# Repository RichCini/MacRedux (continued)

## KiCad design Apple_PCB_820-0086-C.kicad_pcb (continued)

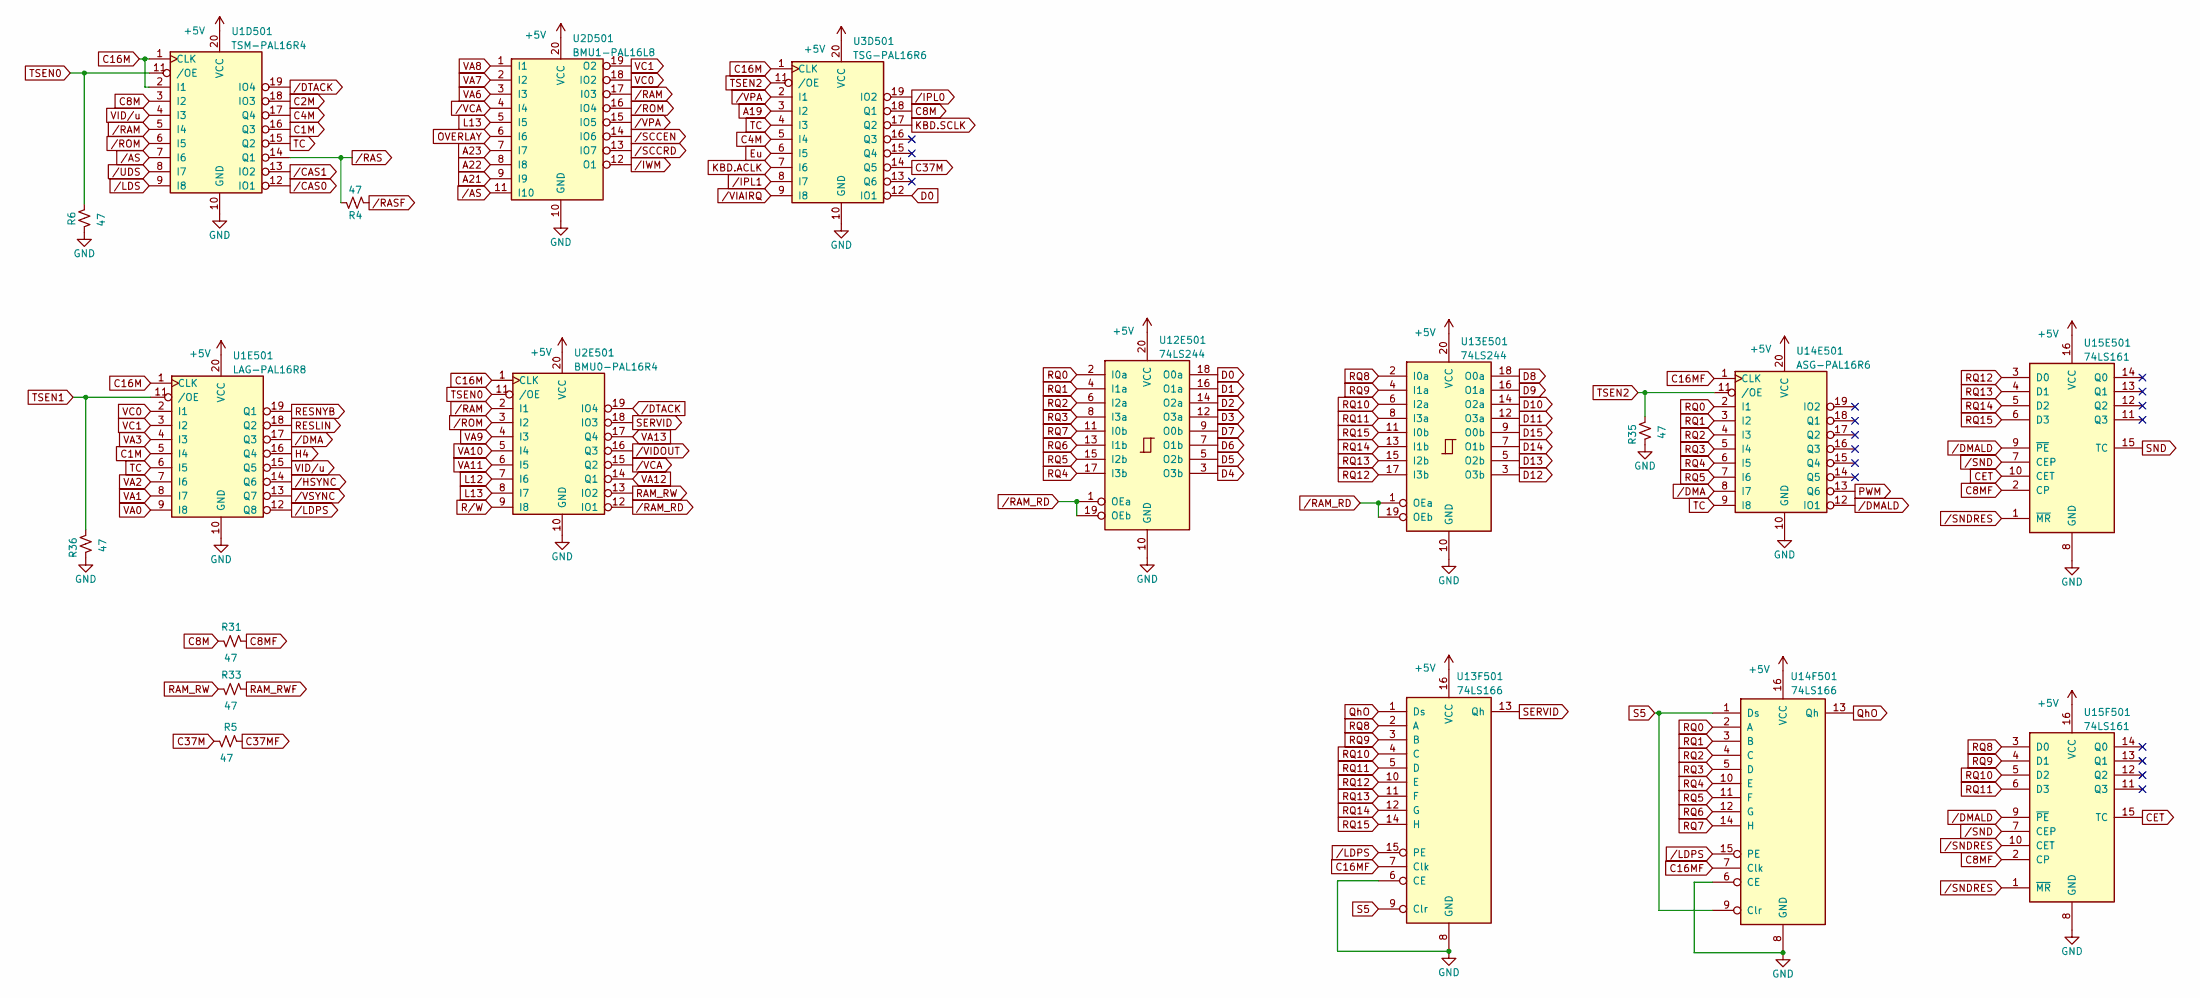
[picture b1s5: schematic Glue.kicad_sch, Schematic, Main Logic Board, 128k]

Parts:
R4, R5, R6, R31, R33, R35, R36: 47; R_Axial_DIN0207_L6.3mm_D2.5mm_P7.62mm_Horizontal
U1D501: TSM-PAL16R4; DIP-20_W7.62mm_Socket_LongPads
U1E501: LAG-PAL16R8; DIP-20_W7.62mm_Socket_LongPads
U2D501: BMU1-PAL16L8; DIP-20_W7.62mm_Socket_LongPads
U2E501: BMU0-PAL16R4; DIP-20_W7.62mm_Socket_LongPads
U3D501: TSG-PAL16R6; DIP-20_W7.62mm_Socket_LongPads
U12E501, U13E501: 74LS244; DIP-20_W7.62mm_Socket_LongPads
U13F501, U14F501: 74LS166; DIP-16_W7.62mm_Socket_LongPads
U14E501: ASG-PAL16R6; DIP-20_W7.62mm_Socket_LongPads
U15E501, U15F501: 74LS161; DIP-16_W7.62mm_Socket_LongPads

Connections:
+5V: U1D501.20 (VCC), U1E501.20 (VCC), U2D501.20 (VCC), U2E501.20 (VCC), U3D501.20 (VCC), U12E501.20 (VCC), U13E501.20 (VCC), U13F501.16 (VCC), U14E501.20 (VCC), U14F501.16 (VCC), U15E501.16 (VCC), U15F501.16 (VCC); also elsewhere on the board
A19: U3D501.3 (I2); also elsewhere on the board
A21: U2D501.9 (I9); also elsewhere on the board
A22: U2D501.8 (I8); also elsewhere on the board
A23: U2D501.7 (I7); also elsewhere on the board
C1M: U1D501.16 (Q3), U1E501.5 (I4)
C2M: U1D501.18 (IO3); also elsewhere on the board
C4M: U1D501.17 (Q4), U3D501.5 (I4)
C8M: R31.1, U1D501.3 (I2), U3D501.18 (Q1)
C8MF: R31.2, U15E501.2 (CP), U15F501.2 (CP); also elsewhere on the board
C16M: U1D501.1 (CLK), U1D501.2 (I1), U1E501.1 (CLK), U2E501.1 (CLK), U3D501.1 (CLK); also elsewhere on the board
C16MF: U13F501.7 (Clk), U14E501.1 (CLK), U14F501.7 (Clk); also elsewhere on the board
C37M: R5.1, U3D501.14 (Q5)
C37MF: R5.2; also elsewhere on the board
CET: U15E501.10 (CET), U15F501.15 (TC)
D0: U3D501.12 (IO1), U12E501.18 (O0a); also elsewhere on the board
D1: U12E501.16 (O1a); also elsewhere on the board
D2: U12E501.14 (O2a); also elsewhere on the board
D3: U12E501.12 (O3a); also elsewhere on the board
D4: U12E501.3 (O3b); also elsewhere on the board
D5: U12E501.5 (O2b); also elsewhere on the board
D6: U12E501.7 (O1b); also elsewhere on the board
D7: U12E501.9 (O0b); also elsewhere on the board
D8: U13E501.18 (O0a); also elsewhere on the board
D9: U13E501.16 (O1a); also elsewhere on the board
D10: U13E501.14 (O2a); also elsewhere on the board
D11: U13E501.12 (O3a); also elsewhere on the board
D12: U13E501.3 (O3b); also elsewhere on the board
D13: U13E501.5 (O2b); also elsewhere on the board
D14: U13E501.7 (O1b); also elsewhere on the board
D15: U13E501.9 (O0b); also elsewhere on the board
Eu: U3D501.6 (I5); also elsewhere on the board
GND: R6.1, R35.1, R36.1, U1D501.10 (GND), U1E501.10 (GND), U2D501.10 (GND), U2E501.10 (GND), U3D501.10 (GND), U12E501.10 (GND), U13E501.10 (GND), U13F501.6 (CE), U13F501.8 (GND), U14E501.10 (GND), U14F501.6 (CE), U14F501.8 (GND), U15E501.8 (GND), U15F501.8 (GND); also elsewhere on the board
H4: U1E501.16 (Q4); also elsewhere on the board
KBD.ACLK: U3D501.7 (I6); also elsewhere on the board
KBD.SCLK: U3D501.17 (Q2); also elsewhere on the board
L12: U2E501.7 (I6); also elsewhere on the board
L13: U2D501.5 (I5), U2E501.8 (I7); also elsewhere on the board
OVERLAY: U2D501.6 (I6); also elsewhere on the board
PWM: U14E501.13 (Q6); also elsewhere on the board
QhO: U13F501.1 (Ds), U14F501.13 (Qh)
RAM_RW: R33.1, U2E501.13 (IO2)
RAM_RWF: R33.2; also elsewhere on the board
RESLIN: U1E501.18 (Q2); also elsewhere on the board
RESNYB: U1E501.19 (Q1); also elsewhere on the board
RQ0: U12E501.2 (I0a), U14E501.2 (I1), U14F501.2 (A); also elsewhere on the board
RQ1: U12E501.4 (I1a), U14E501.3 (I2), U14F501.3 (B); also elsewhere on the board
RQ2: U12E501.6 (I2a), U14E501.4 (I3), U14F501.4 (C); also elsewhere on the board
RQ3: U12E501.8 (I3a), U14E501.5 (I4), U14F501.5 (D); also elsewhere on the board
RQ4: U12E501.17 (I3b), U14E501.6 (I5), U14F501.10 (E); also elsewhere on the board
RQ5: U12E501.15 (I2b), U14E501.7 (I6), U14F501.11 (F); also elsewhere on the board
RQ6: U12E501.13 (I1b), U14F501.12 (G); also elsewhere on the board
RQ7: U12E501.11 (I0b), U14F501.14 (H); also elsewhere on the board
RQ8: U13E501.2 (I0a), U13F501.2 (A), U15F501.3 (D0); also elsewhere on the board
RQ9: U13E501.4 (I1a), U13F501.3 (B), U15F501.4 (D1); also elsewhere on the board
RQ10: U13E501.6 (I2a), U13F501.4 (C), U15F501.5 (D2); also elsewhere on the board
RQ11: U13E501.8 (I3a), U13F501.5 (D), U15F501.6 (D3); also elsewhere on the board
RQ12: U13E501.17 (I3b), U13F501.10 (E), U15E501.3 (D0); also elsewhere on the board
RQ13: U13E501.15 (I2b), U13F501.11 (F), U15E501.4 (D1); also elsewhere on the board
RQ14: U13E501.13 (I1b), U13F501.12 (G), U15E501.5 (D2); also elsewhere on the board
RQ15: U13E501.11 (I0b), U13F501.14 (H), U15E501.6 (D3); also elsewhere on the board
R/W: U2E501.9 (I8); also elsewhere on the board
S5: U13F501.9 (Clr), U14F501.1 (Ds), U14F501.9 (Clr); also elsewhere on the board
SERVID: U2E501.18 (IO3), U13F501.13 (Qh)
SND: U15E501.15 (TC); also elsewhere on the board
TC: U1D501.15 (Q2), U1E501.6 (I5), U3D501.4 (I3), U14E501.9 (I8); also elsewhere on the board
TSEN0: R6.2, U1D501.11 (/OE), U2E501.11 (/OE)
TSEN1: R36.2, U1E501.11 (/OE)
TSEN2: R35.2, U3D501.11 (/OE), U14E501.11 (/OE)
VA0: U1E501.9 (I8); also elsewhere on the board
VA1: U1E501.8 (I7); also elsewhere on the board
VA2: U1E501.7 (I6); also elsewhere on the board
VA3: U1E501.4 (I3); also elsewhere on the board
VA6: U2D501.3 (I3); also elsewhere on the board
VA7: U2D501.2 (I2); also elsewhere on the board
VA8: U2D501.1 (I1); also elsewhere on the board
VA9: U2E501.4 (I3); also elsewhere on the board
VA10: U2E501.5 (I4); also elsewhere on the board
VA11: U2E501.6 (I5); also elsewhere on the board
VA12: U2E501.14 (Q1); also elsewhere on the board
VA13: U2E501.17 (Q4); also elsewhere on the board
VC0: U1E501.2 (I1), U2D501.18 (IO2)
VC1: U1E501.3 (I2), U2D501.19 (O2)
VID/u: U1D501.4 (I3), U1E501.15 (Q5); also elsewhere on the board
/AS: U1D501.7 (I6), U2D501.11 (I10); also elsewhere on the board
/CAS0: U1D501.12 (IO1); also elsewhere on the board
/CAS1: U1D501.13 (IO2); also elsewhere on the board
/DMA: U1E501.17 (Q3), U14E501.8 (I7); also elsewhere on the board
/DMALD: U14E501.12 (IO1), U15E501.9 (~PE), U15F501.9 (~PE)
/DTACK: U1D501.19 (IO4), U2E501.19 (IO4); also elsewhere on the board
/HSYNC: U1E501.14 (Q6); also elsewhere on the board
/IPL0: U3D501.19 (IO2); also elsewhere on the board
/IPL1: U3D501.8 (I7); also elsewhere on the board
/IWM: U2D501.12 (O1); also elsewhere on the board
/LDPS: U1E501.12 (Q8), U13F501.15 (PE), U14F501.15 (PE)
/LDS: U1D501.9 (I8); also elsewhere on the board
/RAM: U1D501.5 (I4), U2D501.17 (I03), U2E501.2 (I1)
/RAM_RD: U2E501.12 (IO1), U12E501.1 (OEa), U12E501.19 (OEb), U13E501.1 (OEa), U13E501.19 (OEb)
/RAS: R4.2, U1D501.14 (Q1)
/RASF: R4.1; also elsewhere on the board
/ROM: U1D501.6 (I5), U2D501.16 (IO4), U2E501.3 (I2); also elsewhere on the board
/SCCEN: U2D501.14 (IO6); also elsewhere on the board
/SCCRD: U2D501.13 (IO7); also elsewhere on the board
/SND: U15E501.7 (CEP), U15F501.7 (CEP); also elsewhere on the board
/SNDRES: U15E501.1 (~MR), U15F501.1 (~MR), U15F501.10 (CET); also elsewhere on the board
/UDS: U1D501.8 (I7); also elsewhere on the board
/VCA: U2D501.4 (I4), U2E501.15 (Q2)
/VIAIRQ: U3D501.9 (I8); also elsewhere on the board
/VIDOUT: U2E501.16 (Q3); also elsewhere on the board
/VPA: U2D501.15 (IO5), U3D501.2 (I1); also elsewhere on the board
/VSYNC: U1E501.13 (Q7); also elsewhere on the board

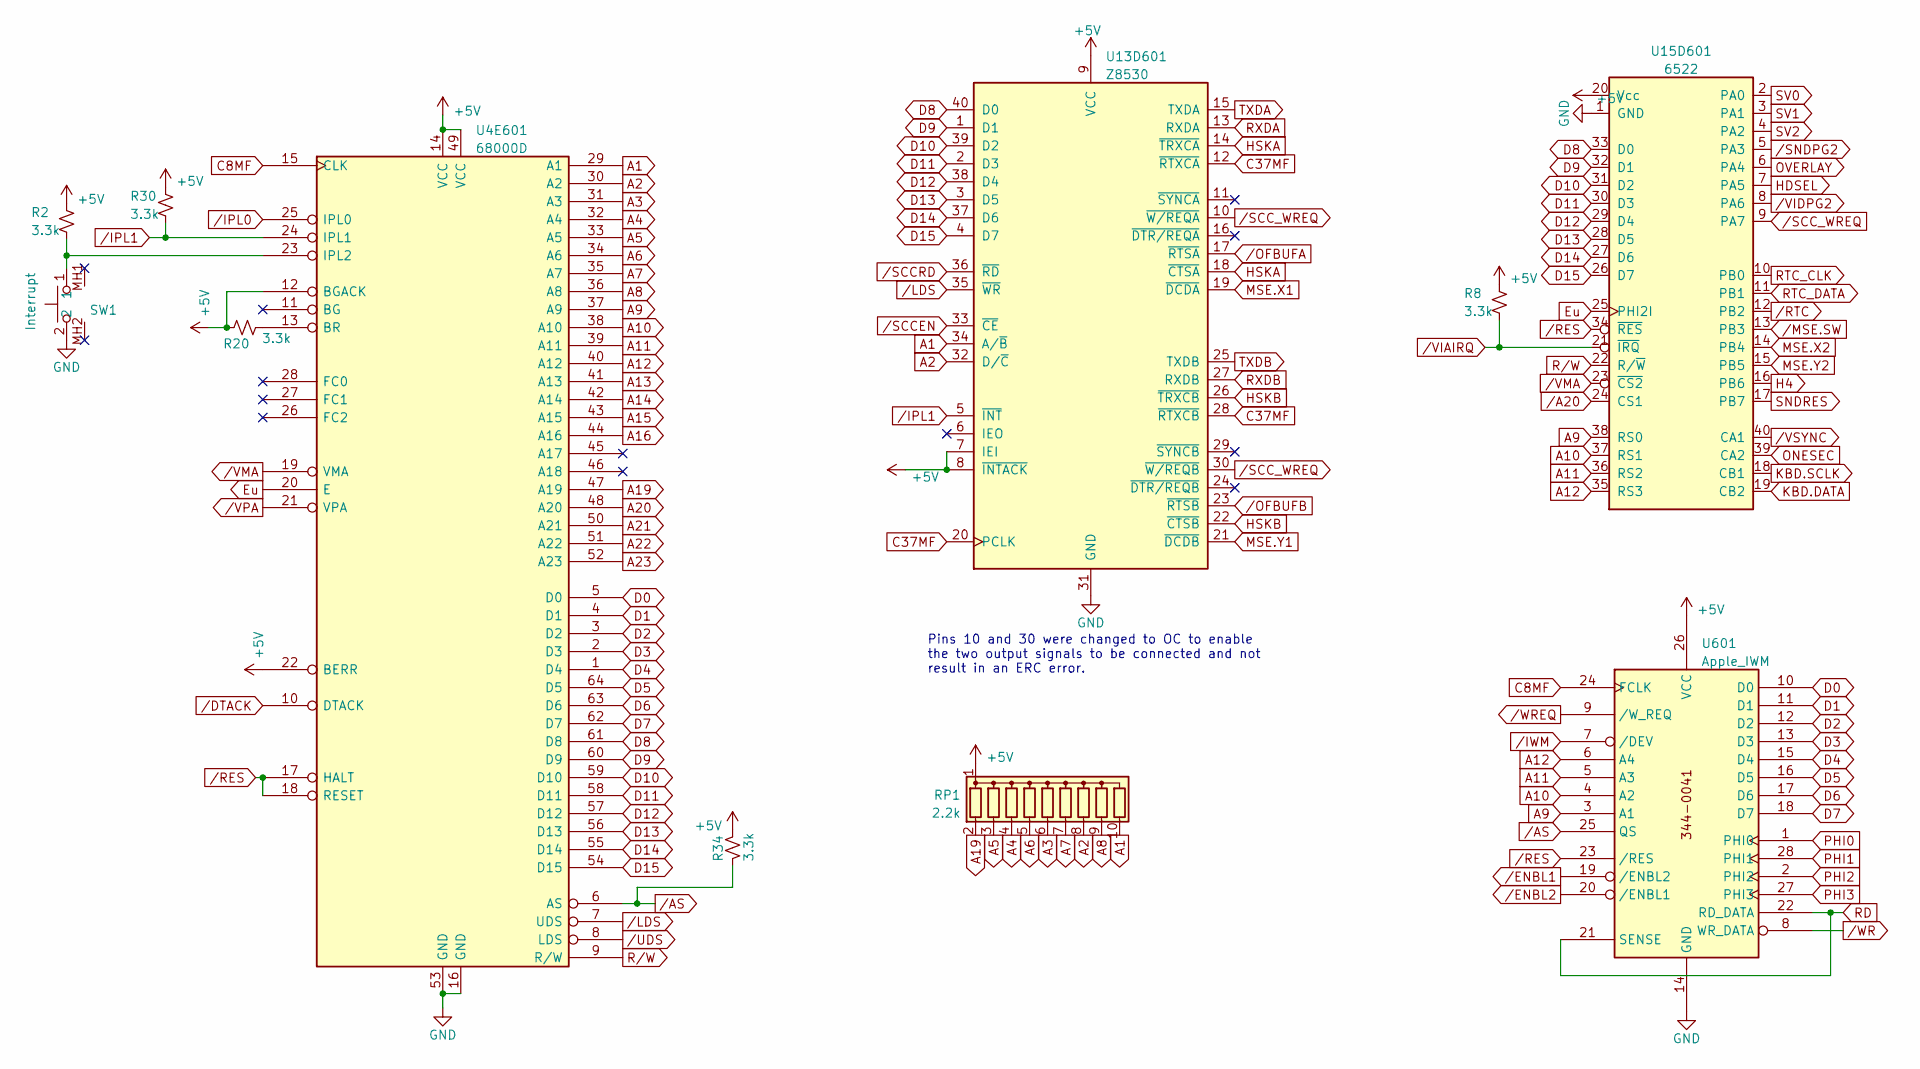
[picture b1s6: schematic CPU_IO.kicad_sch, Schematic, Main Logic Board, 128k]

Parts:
R2, R8, R20, R30, R34: 3.3k; R_Axial_DIN0207_L6.3mm_D2.5mm_P7.62mm_Horizontal
RP1: 2.2k; R_Array_SIP10
SW1: Interrupt; TL1100CF160Q
U4E601: 68000D; DIP-64_W22.86mm_Socket_LongPads
U13D601: Z8530; DIP-40_W15.24mm_Socket_LongPads
U15D601: 6522; DIP-40_W15.24mm_Socket_LongPads
U601: Apple_IWM; DIP-28_W15.24mm_Socket_LongPads

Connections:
+5V: R2.1, R8.1, R20.1, R30.1, R34.1, RP1.1 (common), U4E601.12 (BGACK), U4E601.14 (VCC), U4E601.22 (BERR), U4E601.49 (VCC), U13D601.7 (IEI), U13D601.8 (~INTACK), U13D601.9 (VCC), U15D601.20 (Vcc), U601.26 (VCC); also elsewhere on the board
A1: RP1.10 (R9), U4E601.29 (A1), U13D601.34 (A/~B); also elsewhere on the board
A2: RP1.8 (R7), U4E601.30 (A2), U13D601.32 (D/~C); also elsewhere on the board
A3: RP1.6 (R5), U4E601.31 (A3); also elsewhere on the board
A4: RP1.4 (R3), U4E601.32 (A4); also elsewhere on the board
A5: RP1.3 (R2), U4E601.33 (A5); also elsewhere on the board
A6: RP1.5 (R4), U4E601.34 (A6); also elsewhere on the board
A7: RP1.7 (R6), U4E601.35 (A7); also elsewhere on the board
A8: RP1.9 (R8), U4E601.36 (A8); also elsewhere on the board
A9: U4E601.37 (A9), U15D601.38 (RS0), U601.3 (A1); also elsewhere on the board
A10: U4E601.38 (A10), U15D601.37 (RS1), U601.4 (A2); also elsewhere on the board
A11: U4E601.39 (A11), U15D601.36 (RS2), U601.5 (A3); also elsewhere on the board
A12: U4E601.40 (A12), U15D601.35 (RS3), U601.6 (A4); also elsewhere on the board
A13: U4E601.41 (A13); also elsewhere on the board
A14: U4E601.42 (A14); also elsewhere on the board
A15: U4E601.43 (A15); also elsewhere on the board
A16: U4E601.44 (A16); also elsewhere on the board
A19: RP1.2 (R1), U4E601.47 (A19); also elsewhere on the board
A20: U4E601.48 (A20); also elsewhere on the board
A21: U4E601.50 (A21); also elsewhere on the board
A22: U4E601.51 (A22); also elsewhere on the board
A23: U4E601.52 (A23); also elsewhere on the board
C8MF: U4E601.15 (CLK), U601.24 (FCLK); also elsewhere on the board
C37MF: U13D601.12 (~RTXCA), U13D601.20 (PCLK), U13D601.28 (~RTXCB); also elsewhere on the board
D0: U4E601.5 (D0), U601.10 (D0); also elsewhere on the board
D1: U4E601.4 (D1), U601.11 (D1); also elsewhere on the board
D2: U4E601.3 (D2), U601.12 (D2); also elsewhere on the board
D3: U4E601.2 (D3), U601.13 (D3); also elsewhere on the board
D4: U4E601.1 (D4), U601.15 (D4); also elsewhere on the board
D5: U4E601.64 (D5), U601.16 (D5); also elsewhere on the board
D6: U4E601.63 (D6), U601.17 (D6); also elsewhere on the board
D7: U4E601.62 (D7), U601.18 (D7); also elsewhere on the board
D8: U4E601.61 (D8), U13D601.40 (D0), U15D601.33 (D0); also elsewhere on the board
D9: U4E601.60 (D9), U13D601.1 (D1), U15D601.32 (D1); also elsewhere on the board
D10: U4E601.59 (D10), U13D601.39 (D2), U15D601.31 (D2); also elsewhere on the board
D11: U4E601.58 (D11), U13D601.2 (D3), U15D601.30 (D3); also elsewhere on the board
D12: U4E601.57 (D12), U13D601.38 (D4), U15D601.29 (D4); also elsewhere on the board
D13: U4E601.56 (D13), U13D601.3 (D5), U15D601.28 (D5); also elsewhere on the board
D14: U4E601.55 (D14), U13D601.37 (D6), U15D601.27 (D6); also elsewhere on the board
D15: U4E601.54 (D15), U13D601.4 (D7), U15D601.26 (D7); also elsewhere on the board
Eu: U4E601.20 (E), U15D601.25 (PHI2I); also elsewhere on the board
GND: SW1.2, U4E601.16 (GND), U4E601.53 (GND), U13D601.31 (GND), U15D601.1 (GND), U601.14 (GND); also elsewhere on the board
H4: U15D601.16 (PB6); also elsewhere on the board
HDSEL: U15D601.7 (PA5); also elsewhere on the board
HSKA: U13D601.14 (~TRXCA), U13D601.18 (~CTSA); also elsewhere on the board
HSKB: U13D601.22 (~CTSB), U13D601.26 (~TRXCB); also elsewhere on the board
KBD.DATA: U15D601.19 (CB2); also elsewhere on the board
KBD.SCLK: U15D601.18 (CB1); also elsewhere on the board
MSE.X1: U13D601.19 (~DCDA); also elsewhere on the board
MSE.X2: U15D601.14 (PB4); also elsewhere on the board
MSE.Y1: U13D601.21 (~DCDB); also elsewhere on the board
MSE.Y2: U15D601.15 (PB5); also elsewhere on the board
unnamed: R2.2, SW1.1, U4E601.23 (IPL2)
unnamed: R20.2, U4E601.13 (BR)
ONESEC: U15D601.39 (CA2); also elsewhere on the board
OVERLAY: U15D601.6 (PA4); also elsewhere on the board
PHI0: U601.1 (PHI0); also elsewhere on the board
PHI1: U601.28 (PHI1); also elsewhere on the board
PHI2: U601.2 (PHI2); also elsewhere on the board
PHI3: U601.27 (PHI3); also elsewhere on the board
RD: U601.21 (SENSE), U601.22 (RD_DATA); also elsewhere on the board
RTC_CLK: U15D601.10 (PB0); also elsewhere on the board
RTC_DATA: U15D601.11 (PB1); also elsewhere on the board
RXDA: U13D601.13 (RXDA); also elsewhere on the board
RXDB: U13D601.27 (RXDB); also elsewhere on the board
R/W: U4E601.9 (R/W), U15D601.22 (R/~W); also elsewhere on the board
SNDRES: U15D601.17 (PB7); also elsewhere on the board
SV0: U15D601.2 (PA0); also elsewhere on the board
SV1: U15D601.3 (PA1); also elsewhere on the board
SV2: U15D601.4 (PA2); also elsewhere on the board
TXDA: U13D601.15 (TXDA); also elsewhere on the board
TXDB: U13D601.25 (TXDB); also elsewhere on the board
/A20: U15D601.24 (CS1); also elsewhere on the board
/AS: R34.2, U4E601.6 (AS), U601.25 (QS); also elsewhere on the board
/DTACK: U4E601.10 (DTACK); also elsewhere on the board
/ENBL1: U601.19 (/ENBL2); also elsewhere on the board
/ENBL2: U601.20 (/ENBL1); also elsewhere on the board
/IPL0: U4E601.25 (IPL0); also elsewhere on the board
/IPL1: R30.2, U4E601.24 (IPL1), U13D601.5 (~INT); also elsewhere on the board
/IWM: U601.7 (/DEV); also elsewhere on the board
/LDS: U4E601.7 (UDS), U13D601.35 (~WR); also elsewhere on the board
/MSE.SW: U15D601.13 (PB3); also elsewhere on the board
/OFBUFA: U13D601.17 (~RTSA); also elsewhere on the board
/OFBUFB: U13D601.23 (~RTSB); also elsewhere on the board
/RES: U4E601.17 (HALT), U4E601.18 (RESET), U15D601.34 (~RES), U601.23 (/RES); also elsewhere on the board
/RTC: U15D601.12 (PB2); also elsewhere on the board
/SCCEN: U13D601.33 (~CE); also elsewhere on the board
/SCCRD: U13D601.36 (~RD); also elsewhere on the board
/SCC_WREQ: U13D601.10 (~W/REQA), U13D601.30 (~W/REQB), U15D601.9 (PA7)
/SNDPG2: U15D601.5 (PA3); also elsewhere on the board
/UDS: U4E601.8 (LDS); also elsewhere on the board
/VIAIRQ: R8.2, U15D601.21 (~IRQ); also elsewhere on the board
/VIDPG2: U15D601.8 (PA6); also elsewhere on the board
/VMA: U4E601.19 (VMA), U15D601.23 (~CS2)
/VPA: U4E601.21 (VPA); also elsewhere on the board
/VSYNC: U15D601.40 (CA1); also elsewhere on the board
/WR: U601.8 (WR_DATA); also elsewhere on the board
/WREQ: U601.9 (/W_REQ); also elsewhere on the board

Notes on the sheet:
Pins 10 and 30 were changed to OC to enable the two output signals to be connected and not result in an ERC error.

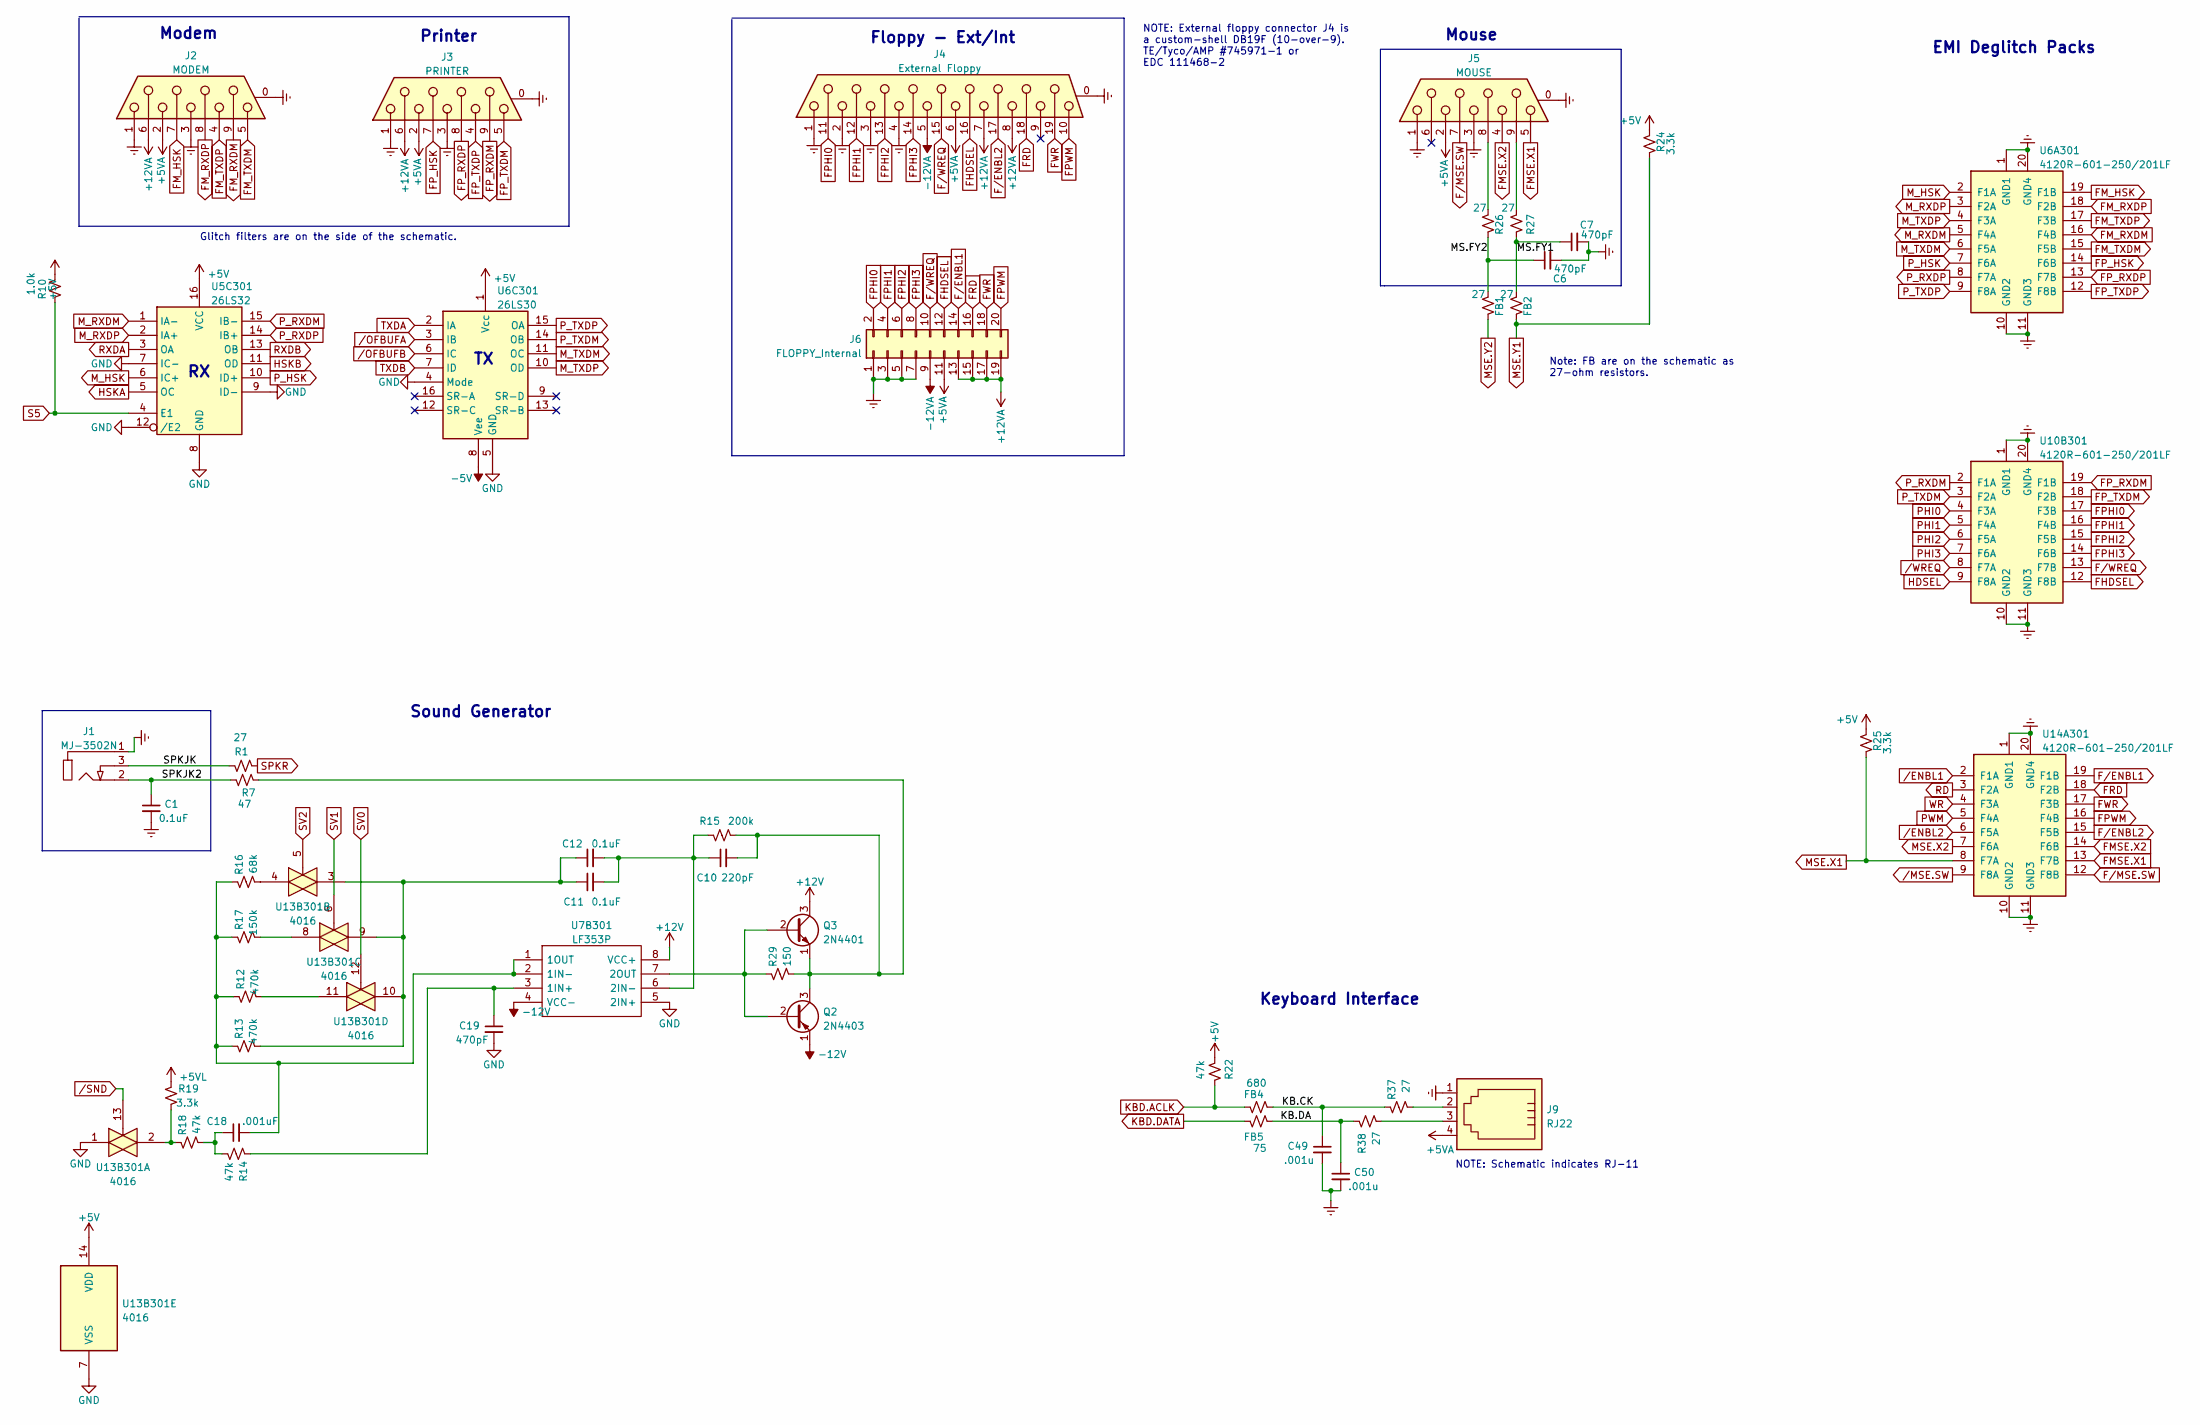
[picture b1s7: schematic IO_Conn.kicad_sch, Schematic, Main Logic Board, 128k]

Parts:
C1, C11, C12: 0.1uF; C_Axial_L3.8mm_D2.6mm_P7.50mm_Horizontal
C6, C7, C19: 470pF; C_Axial_L3.8mm_D2.6mm_P7.50mm_Horizontal
C10: 220pF; C_Axial_L3.8mm_D2.6mm_P7.50mm_Horizontal
C18: .001uF; C_Axial_L3.8mm_D2.6mm_P7.50mm_Horizontal
C49, C50: .001u; C_Axial_L3.8mm_D2.6mm_P7.50mm_Horizontal
FB1, FB2: 27; R_Axial_DIN0207_L6.3mm_D2.5mm_P7.62mm_Horizontal
FB4: 680; R_Axial_DIN0207_L6.3mm_D2.5mm_P7.62mm_Horizontal
FB5: 75; R_Axial_DIN0207_L6.3mm_D2.5mm_P7.62mm_Horizontal
J1: MJ-3502N; MJ3502N; Mouser Part Number 490-MJ-3502N
J2: MODEM; DSUB-9_Female_Horizontal_P2.77x2.84mm_EdgePinOffset4.94mm_H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
J3: PRINTER; DSUB-9_Female_Horizontal_P2.77x2.84mm_EdgePinOffset4.94mm_H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
J4: External Floppy; DSUB-19_Female_Horizontal_P2.77x2.84mm_EdgePinOffset7.70mm_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
J5: MOUSE; DSUB-9_Female_Horizontal_P2.77x2.84mm_EdgePinOffset4.94mm_H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
J6: FLOPPY_Internal; IDC-Header_2x10_P2.54mm_Vertical
J9: RJ22; 55559801
Q2: 2N4403; TO-92_Inline
Q3: 2N4401; TO-92_Inline
R1, R26, R27, R37, R38: 27; R_Axial_DIN0207_L6.3mm_D2.5mm_P7.62mm_Horizontal
R7: 47; R_Axial_DIN0207_L6.3mm_D2.5mm_P7.62mm_Horizontal
R10: 1.0k; R_Axial_DIN0207_L6.3mm_D2.5mm_P7.62mm_Horizontal
R12, R13: 470k; R_Axial_DIN0207_L6.3mm_D2.5mm_P7.62mm_Horizontal
R14, R18, R22: 47k; R_Axial_DIN0207_L6.3mm_D2.5mm_P7.62mm_Horizontal
R15: 200k; R_Axial_DIN0207_L6.3mm_D2.5mm_P7.62mm_Horizontal
R16: 68k; R_Axial_DIN0207_L6.3mm_D2.5mm_P7.62mm_Horizontal
R17: 150k; R_Axial_DIN0207_L6.3mm_D2.5mm_P7.62mm_Horizontal
R19, R24, R25: 3.3k; R_Axial_DIN0207_L6.3mm_D2.5mm_P7.62mm_Horizontal
R29: 150; R_Axial_DIN0207_L6.3mm_D2.5mm_P7.62mm_Horizontal
U5C301: 26LS32; DIP-16_W7.62mm_Socket_LongPads
U6A301, U10B301, U14A301: 4120R-601-250/201LF; DIP-20_W7.62mm_Socket_LongPads
U6C301: 26LS30; DIP-16_W7.62mm_Socket_LongPads
U7B301: LF353P; DIP-8_W7.62mm_Socket_LongPads; Mouser Part Number 595-LF353P
U13B301: 4016; DIP-14_W7.62mm_Socket_LongPads

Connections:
+5V: R10.1, R22.1, R24.1, R25.1, U5C301.16 (VCC), U6C301.1 (Vcc), U13B301.14 (VDD); also elsewhere on the board
+5VA: J2.2, J3.2, J4.6, J5.2, J6.11, J9.4; also elsewhere on the board
+5VL: R19.1; also elsewhere on the board
+12V: Q3.3 (C), U7B301.8 (VCC+); also elsewhere on the board
+12VA: J2.6, J3.6, J4.7, J4.8, J6.13, J6.15, J6.17, J6.19; also elsewhere on the board
-5V: U6C301.8 (Vee); also elsewhere on the board
-12V: Q2.1 (E), U7B301.4 (VCC-); also elsewhere on the board
-12VA: J4.5, J6.9; also elsewhere on the board
/IO Connectors/KB.CK: C49.1, FB4.2, R37.1
/IO Connectors/KB.DA: C50.1, FB5.2, R38.1
/IO Connectors/MS.FY1: C7.1, FB2.2, R27.1
/IO Connectors/MS.FY2: C6.1, FB1.2, R26.1
/IO Connectors/SPKJK: J1.3, R1.1
/IO Connectors/SPKJK2: C1.1, J1.2, R7.1
Earth: C1.2, C6.2, C7.2, C49.2, C50.2, J1.1, J2.0 (PAD), J2.1, J2.3, J3.0 (PAD), J3.1, J3.3, J4.0 (PAD), J4.1, J4.2, J4.3, J4.4, J5.0 (PAD), J5.1, J5.3, J6.1, J6.3, J6.5, J6.7, J9.1, U6A301.1 (GND1), U6A301.10 (GND2), U6A301.11 (GND3), U6A301.20 (GND4), U10B301.1 (GND1), U10B301.10 (GND2), U10B301.11 (GND3), U10B301.20 (GND4), U14A301.1 (GND1), U14A301.10 (GND2), U14A301.11 (GND3), U14A301.20 (GND4); also elsewhere on the board
FHDSEL: J4.16, J6.12, U10B301.12 (F8B)
FMSE.X1: J5.5, U14A301.13 (F7B)
FMSE.X2: J5.4, U14A301.14 (F6B)
FM_HSK: J2.7, U6A301.19 (F1B)
FM_RXDM: J2.9, U6A301.16 (F4B)
FM_RXDP: J2.8, U6A301.18 (F2B)
FM_TXDM: J2.5, U6A301.15 (F5B)
FM_TXDP: J2.4, U6A301.17 (F3B)
FPHI0: J4.11, J6.2, U10B301.17 (F3B)
FPHI1: J4.12, J6.4, U10B301.16 (F4B)
FPHI2: J4.13, J6.6, U10B301.15 (F5B)
FPHI3: J4.14, J6.8, U10B301.14 (F6B)
FPWM: J4.10, J6.20, U14A301.16 (F4B)
FP_HSK: J3.7, U6A301.14 (F6B)
FP_RXDM: J3.9, U10B301.19 (F1B)
FP_RXDP: J3.8, U6A301.13 (F7B)
FP_TXDM: J3.5, U10B301.18 (F2B)
FP_TXDP: J3.4, U6A301.12 (F8B)
FRD: J4.18, J6.16, U14A301.18 (F2B)
FWR: J4.19, J6.18, U14A301.17 (F3B)
F/ENBL1: J6.14, U14A301.19 (F1B)
F/ENBL2: J4.17, U14A301.15 (F5B)
F/MSE.SW: J5.7, U14A301.12 (F8B)
F/WREQ: J4.15, J6.10, U10B301.13 (F7B)
GND: C19.2, U5C301.7 (IC-), U5C301.8 (GND), U5C301.9 (ID-), U5C301.12 (/E2), U6C301.4 (Mode), U6C301.5 (GND), U7B301.5 (2IN+), U13B301.1, U13B301.7 (VSS); also elsewhere on the board
HDSEL: U10B301.9 (F8A); also elsewhere on the board
HSKA: U5C301.5 (OC); also elsewhere on the board
HSKB: U5C301.11 (OD); also elsewhere on the board
KBD.ACLK: FB4.1, R22.2; also elsewhere on the board
KBD.DATA: FB5.1; also elsewhere on the board
MSE.X1: R25.2, U14A301.8 (F7A); also elsewhere on the board
MSE.X2: U14A301.7 (F6A); also elsewhere on the board
MSE.Y1: FB2.1, R24.2; also elsewhere on the board
MSE.Y2: FB1.1; also elsewhere on the board
M_HSK: U5C301.6 (IC+), U6A301.2 (F1A)
M_RXDM: U5C301.1 (IA-), U6A301.5 (F4A)
M_RXDP: U5C301.2 (IA+), U6A301.3 (F2A)
M_TXDM: U6A301.6 (F5A), U6C301.11 (OC)
M_TXDP: U6A301.4 (F3A), U6C301.10 (OD)
unnamed: C10.1, C11.2, C12.2, R15.1, U7B301.6 (2IN-)
unnamed: C10.2, Q2.3 (C), Q3.1 (E), R7.2, R15.2, R29.2
unnamed: C11.1, C12.1, R13.2, U13B301.3, U13B301.9, U13B301.10
unnamed: C18.1, R14.2, R18.2
unnamed: C18.2, R12.1, R13.1, R16.1, R17.1, U7B301.1 (1OUT), U7B301.2 (1IN-)
unnamed: C19.1, R14.1, U7B301.3 (1IN+)
unnamed: J5.8, R26.2
unnamed: J5.9, R27.2
unnamed: J9.2, R37.2
unnamed: J9.3, R38.2
unnamed: Q2.2 (B), Q3.2 (B), R29.1, U7B301.7 (2OUT)
unnamed: R12.2, U13B301.11
unnamed: R16.2, U13B301.4
unnamed: R17.2, U13B301.8
unnamed: R18.1, R19.2, U13B301.2
PHI0: U10B301.4 (F3A); also elsewhere on the board
PHI1: U10B301.5 (F4A); also elsewhere on the board
PHI2: U10B301.6 (F5A); also elsewhere on the board
PHI3: U10B301.7 (F6A); also elsewhere on the board
PWM: U14A301.5 (F4A); also elsewhere on the board
P_HSK: U5C301.10 (ID+), U6A301.7 (F6A)
P_RXDM: U5C301.15 (IB-), U10B301.2 (F1A)
P_RXDP: U5C301.14 (IB+), U6A301.8 (F7A)
P_TXDM: U6C301.14 (OB), U10B301.3 (F2A)
P_TXDP: U6A301.9 (F8A), U6C301.15 (OA)
RD: U14A301.3 (F2A); also elsewhere on the board
RXDA: U5C301.3 (OA); also elsewhere on the board
RXDB: U5C301.13 (OB); also elsewhere on the board
S5: R10.2, U5C301.4 (E1); also elsewhere on the board
SPKR: R1.2; also elsewhere on the board
SV0: U13B301.12; also elsewhere on the board
SV1: U13B301.6; also elsewhere on the board
SV2: U13B301.5; also elsewhere on the board
TXDA: U6C301.2 (IA); also elsewhere on the board
TXDB: U6C301.7 (ID); also elsewhere on the board
WR: U14A301.4 (F3A); also elsewhere on the board
/ENBL1: U14A301.2 (F1A); also elsewhere on the board
/ENBL2: U14A301.6 (F5A); also elsewhere on the board
/MSE.SW: U14A301.9 (F8A); also elsewhere on the board
/OFBUFA: U6C301.3 (IB); also elsewhere on the board
/OFBUFB: U6C301.6 (IC); also elsewhere on the board
/SND: U13B301.13; also elsewhere on the board
/WREQ: U10B301.8 (F7A); also elsewhere on the board

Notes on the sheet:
Note: FB are on the schematic as 27-ohm resistors.
Floppy - Ext/Int
Modem
Keyboard Interface
Printer
NOTE: Schematic indicates RJ-11
Glitch filters are on the side of the schematic.
Sound Generator
NOTE: External floppy connector J4 is a custom-shell DB19F (10-over-9). TE/Tyco/AMP #745971-1 or EDC 111468-2
EMI Deglitch Packs
Mouse

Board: 4 copper layers, 186 parts (0 on the bottom side), 262 nets, no tracks yet.

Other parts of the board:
G001, G002: LOGO

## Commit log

2023-08-28 Add files via upload
    After obtaining actual 128k board, certain component placement tweaks were made. Board was re-routed based on those changes.
